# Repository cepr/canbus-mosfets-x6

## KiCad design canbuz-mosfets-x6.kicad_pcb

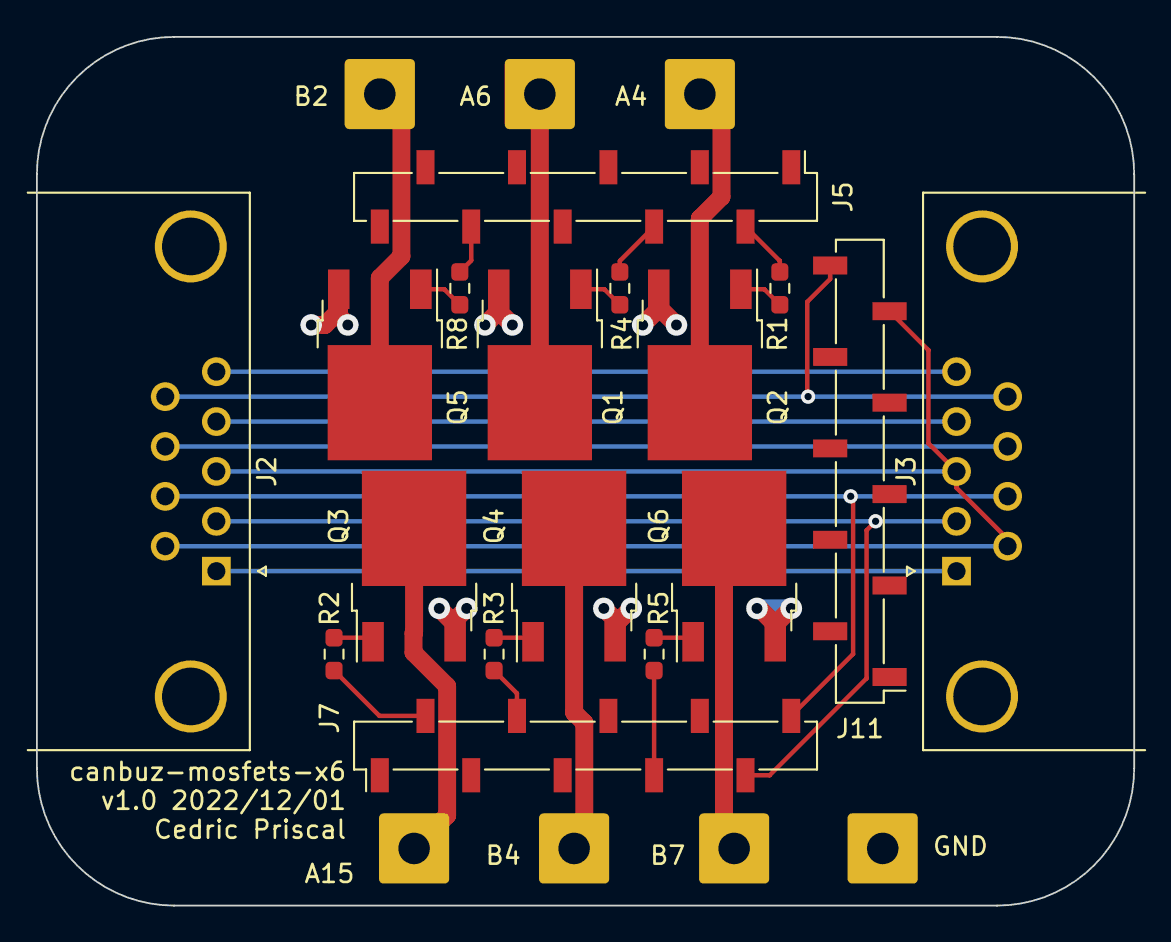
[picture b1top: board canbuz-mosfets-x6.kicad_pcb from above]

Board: 2 copper layers, 61.0 x 48.3 mm, 24 parts (0 on the bottom side), 26 nets.

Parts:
J1, J4, J6, J8, J9, J10, J12: Conn_01x01; SolderWire-1sqmm_1x01_D1.4mm_OD3.9mm
J2: DB9_Female_MountingHoles; DSUB-9_Female_Horizontal_P2.77x2.84mm_EdgePinOffset7.70mm_H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
J3: DB9_Male_MountingHoles; DSUB-9_Male_Horizontal_P2.77x2.84mm_EdgePinOffset7.70mm_Hou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
J5, J7, J11: Conn_01x10; PinSocket_1x10_P2.54mm_Vertical_SMD_Pin1Left
Q1, Q2, Q3, Q4, Q5, Q6: AOD4184A; TO-252-2
R1, R2, R3, R4, R5, R8: 100; R_0603_1608Metric_Pad0.98x0.95mm_HandSolder

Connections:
CANH: J2.7, J3.7, J7.10
CANL: J2.2, J3.2, J7.9
GND: J2.3, J2.6, J3.3, J3.6, J11.9
GNDPWR: J2.0 (PAD), J2.5, J3.0 (PAD), J3.5, J6.1, Q1.3 (S), Q2.3 (S), Q3.3 (S), Q4.3 (S), Q5.3 (S), Q6.3 (S)
unnamed: J1.1, Q2.2 (D)
unnamed: J2.1, J3.1
unnamed: J2.4, J3.4
unnamed: J2.8, J3.8
unnamed: J4.1, Q1.2 (D)
unnamed: J8.1, Q5.2 (D)
unnamed: J9.1, Q3.2 (D)
unnamed: J10.1, Q4.2 (D)
unnamed: J12.1, Q6.2 (D)
unnamed: Q1.1 (G), R4.2
unnamed: Q2.1 (G), R1.2
unnamed: Q3.1 (G), R2.2
unnamed: Q4.1 (G), R3.2
unnamed: Q5.1 (G), R8.2
unnamed: Q6.1 (G), R5.2
PA4: J5.2, R1.1
PA6: J5.4, R4.1
PA15: J7.2, R2.1
PB2: J5.8, R8.1
PB4: J7.4, R3.1
PB7: J7.7, R5.1
VIN: J2.9, J3.9, J11.10

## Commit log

2022-12-02 v1.0
2022-12-07 Adding BOM
2023-06-10 Renaming project
